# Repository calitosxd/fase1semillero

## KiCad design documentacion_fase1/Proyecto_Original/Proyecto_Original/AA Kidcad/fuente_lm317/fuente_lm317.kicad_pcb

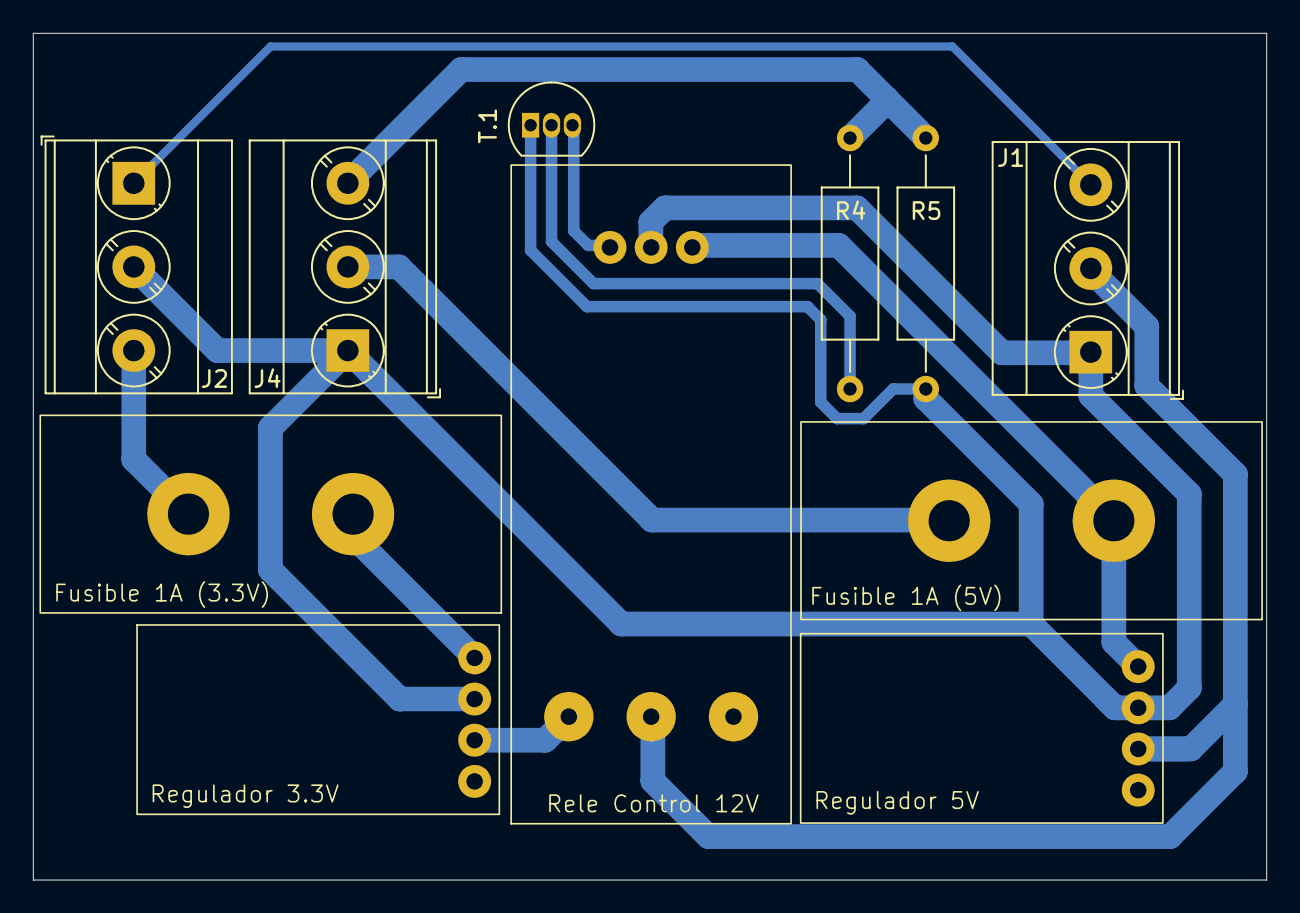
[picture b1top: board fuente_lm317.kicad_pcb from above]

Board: 2 copper layers, 74.9 x 51.4 mm, 11 parts (0 on the bottom side), 11 nets.

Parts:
Fusible 1A (3.3V), Fusible 1A (5V): Porta_Fusible
J1: V. Entrada 12V; TerminalBlock_Phoenix_MKDS-3-3-5.08_1x03_P5.08mm_Horizontal
J2: Salida 3.3V; TerminalBlock_Phoenix_MKDS-3-3-5.08_1x03_P5.08mm_Horizontal
J4: Salida 5V; TerminalBlock_Phoenix_MKDS-3-3-5.08_1x03_P5.08mm_Horizontal
R4: 1k; R_Axial_DIN0309_L9.0mm_D3.2mm_P15.24mm_Horizontal
R5: 10k; R_Axial_DIN0309_L9.0mm_D3.2mm_P15.24mm_Horizontal
Regulador 3.3V, Regulador 5V: DC-DC_Buck
Rele Control 12V: Relevo_Bajo
T.1: 2N3904; TO-92_Inline

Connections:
3.3 v: Fusible 1A (3.3V).1 (In), Regulador 3.3V.1 (VO+)
5v: Fusible 1A (5V).1 (In), Regulador 5V.1 (VO+), Rele Control 12V.3 (VCC)
12V: Regulador 3.3V.3 (IN+), Rele Control 12V.4 (NO)
+12V: J1.2, Regulador 5V.3 (IN+), Rele Control 12V.5 (COM)
Control_VCC_Sensor: J4.3, R4.2, R5.2
GND: J1.1, J2.2, J4.1, R5.1, Regulador 3.3V.2 (GND), Regulador 5V.2 (GND), Rele Control 12V.2 (GND), T.1.1 (E)
GNDPWR: J1.3, J2.1
unnamed: Fusible 1A (3.3V).2 (Out), J2.3
unnamed: Fusible 1A (5V).2 (Out), J4.2
unnamed: R4.1, T.1.2 (B)
unnamed: Rele Control 12V.1 (IN), T.1.3 (C)
